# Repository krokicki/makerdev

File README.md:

# [MakerDev](http://makerdev.com) 

Here you will find 3d models (STL, OpenSCAD) for 3d printing, circuit board schematics (EAGLE), and code for various maker projects. These resources are made available by [makerdev.com](http://makerdev.com).

## Copyright and License

Copyright 2015 Konrad Rokicki

Licensed under CC BY-SA 3.0 US. See LICENSE.txt for more information.

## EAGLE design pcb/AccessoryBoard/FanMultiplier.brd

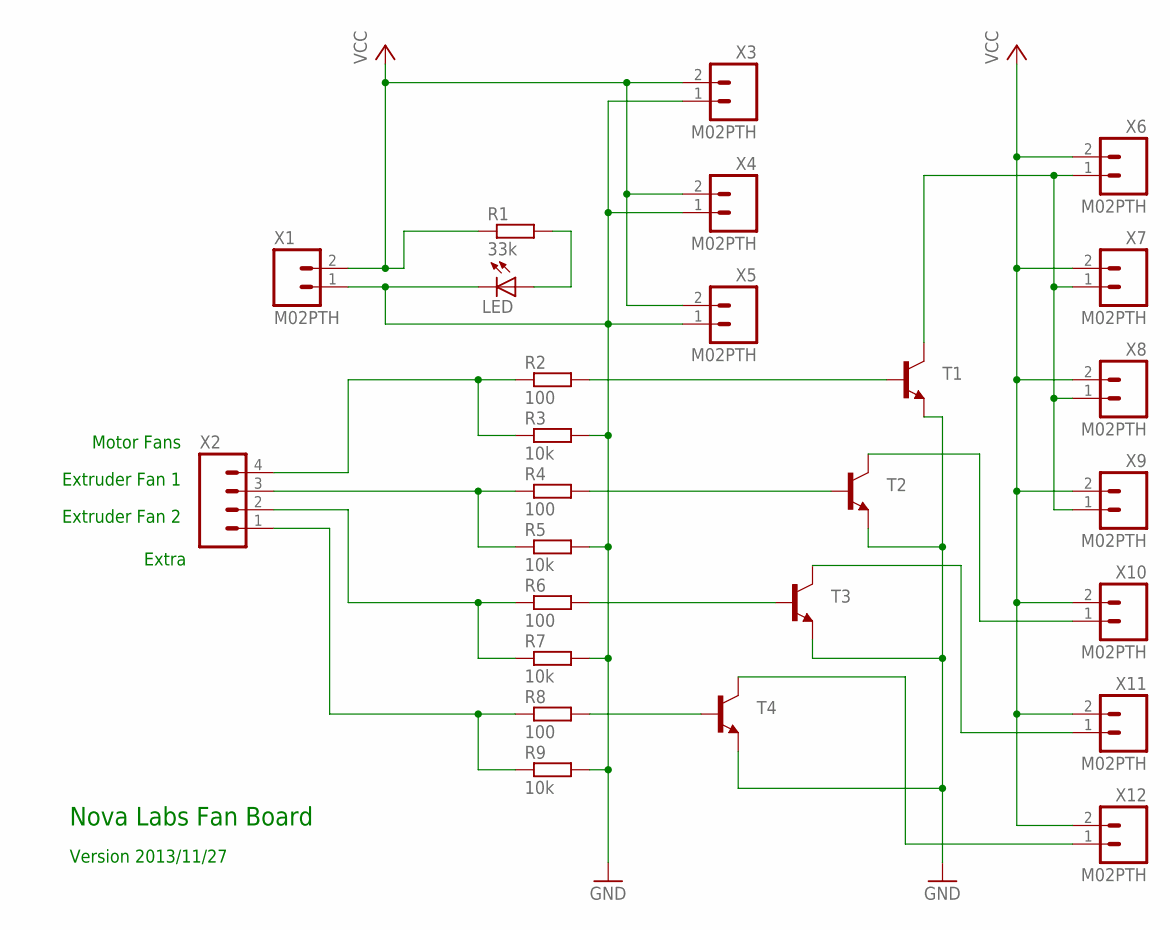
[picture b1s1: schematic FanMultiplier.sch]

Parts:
LED: LED3MM
R1: 33k; 0207/7
R2, R4, R6, R8: 100; 0207/7
R3, R5, R7, R9: 10k; 0207/7
T1, T2, T3, T4: TRANSISTOR_NPNTO92; TO-92
X1, X3, X4, X5, X6, X7, X8, X9, X10, X11, X12: M02PTH; 1X02
X2: M04PTH; 1X04

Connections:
GND: LED.K (C), R3.2, R5.2, R7.2, R9.2, T1.1 (E), T2.1 (E), T3.1 (E), T4.1 (E), X1.1, X3.1, X4.1, X5.1
unnamed: R2.2, T1.2 (B)
unnamed: R4.2, T2.2 (B)
unnamed: R6.2, T3.2 (B)
unnamed: LED.A, R1.2
unnamed: R2.1, R3.1, X2.4
unnamed: R4.1, R5.1, X2.3
unnamed: R6.1, R7.1, X2.2
unnamed: R8.1, R9.1, X2.1
unnamed: R8.2, T4.2 (B)
unnamed: T4.3 (C), X12.1
unnamed: T1.3 (C), X6.1, X7.1, X8.1, X9.1
unnamed: T2.3 (C), X10.1
unnamed: T3.3 (C), X11.1
VCC: R1.1, X1.2, X3.2, X4.2, X5.2, X6.2, X7.2, X8.2, X9.2, X10.2, X11.2, X12.2

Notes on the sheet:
Extruder Fan 1
Extruder Fan 2
Motor Fans
Extra
Nova Labs Fan Board
Version 2013/11/27

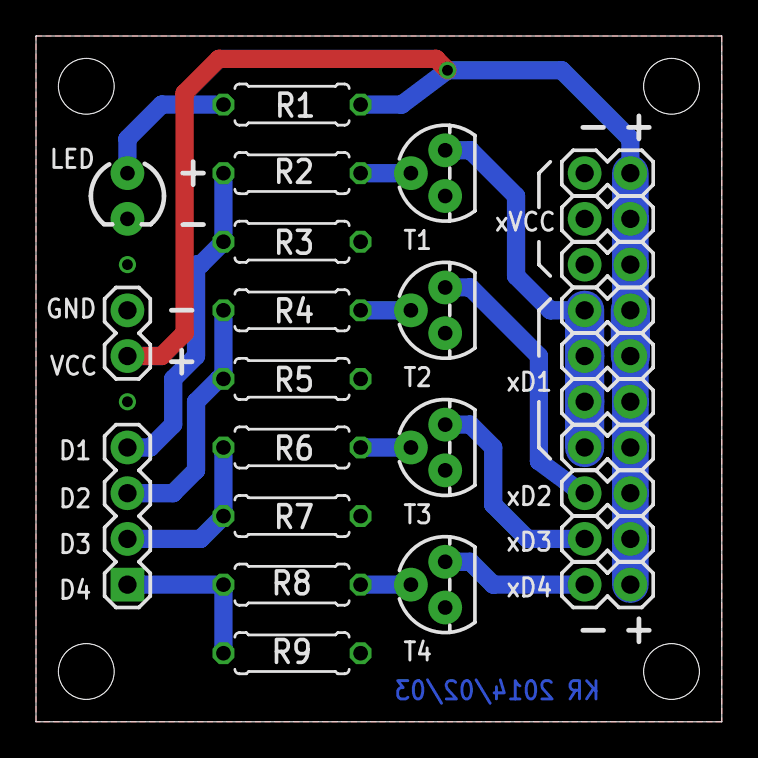
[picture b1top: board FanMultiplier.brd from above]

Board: 2 copper layers, 38.1 x 38.1 mm, 26 parts (0 on the bottom side), 15 nets.

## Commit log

2014-02-09 added fan mounts
2014-02-09 updated license
2014-02-09 fixed render
2014-04-07 cleaned up edges
2014-04-07 changed to monthly log files added comments
2014-04-12 added 20 one-wire sensors
2014-05-03 fixed sensor read
2014-05-03 initial design
2014-05-03 added vcc outputs added 4th pwm output
2014-05-03 minor routing improvements
2014-05-03 brought headers together for easier soldering replaced logo with text other minor improvements
2014-05-03 resized mounting holes better silkscreen annotations minor routing improvements
2014-09-28 added new Fat32 version of SD card browser, with Python interface
2015-04-04 request temperatures each time
2015-04-04 new version of logger
2015-05-26 initial commit of working hive visualization
2015-05-26 split text into side renderer added custom camera
2015-06-05 better support for offscreen rendering text annotations
2015-07-12 simple script for rendering frames to a movie
2015-07-12 better support for year-long time scales CLI arguments
2015-08-17 added notebook, moved code out of viz subdirectory
2016-03-02 added Gerber files for SeeedStudio Fusion PCB
2016-05-24 added PDF versions of accessory board
2018-07-19 improvements

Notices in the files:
parts and their libraries:
SparkFun-Connectors: Licensing: CC v3.0 Share-Alike You are welcome to use this library for commercial purposes.
